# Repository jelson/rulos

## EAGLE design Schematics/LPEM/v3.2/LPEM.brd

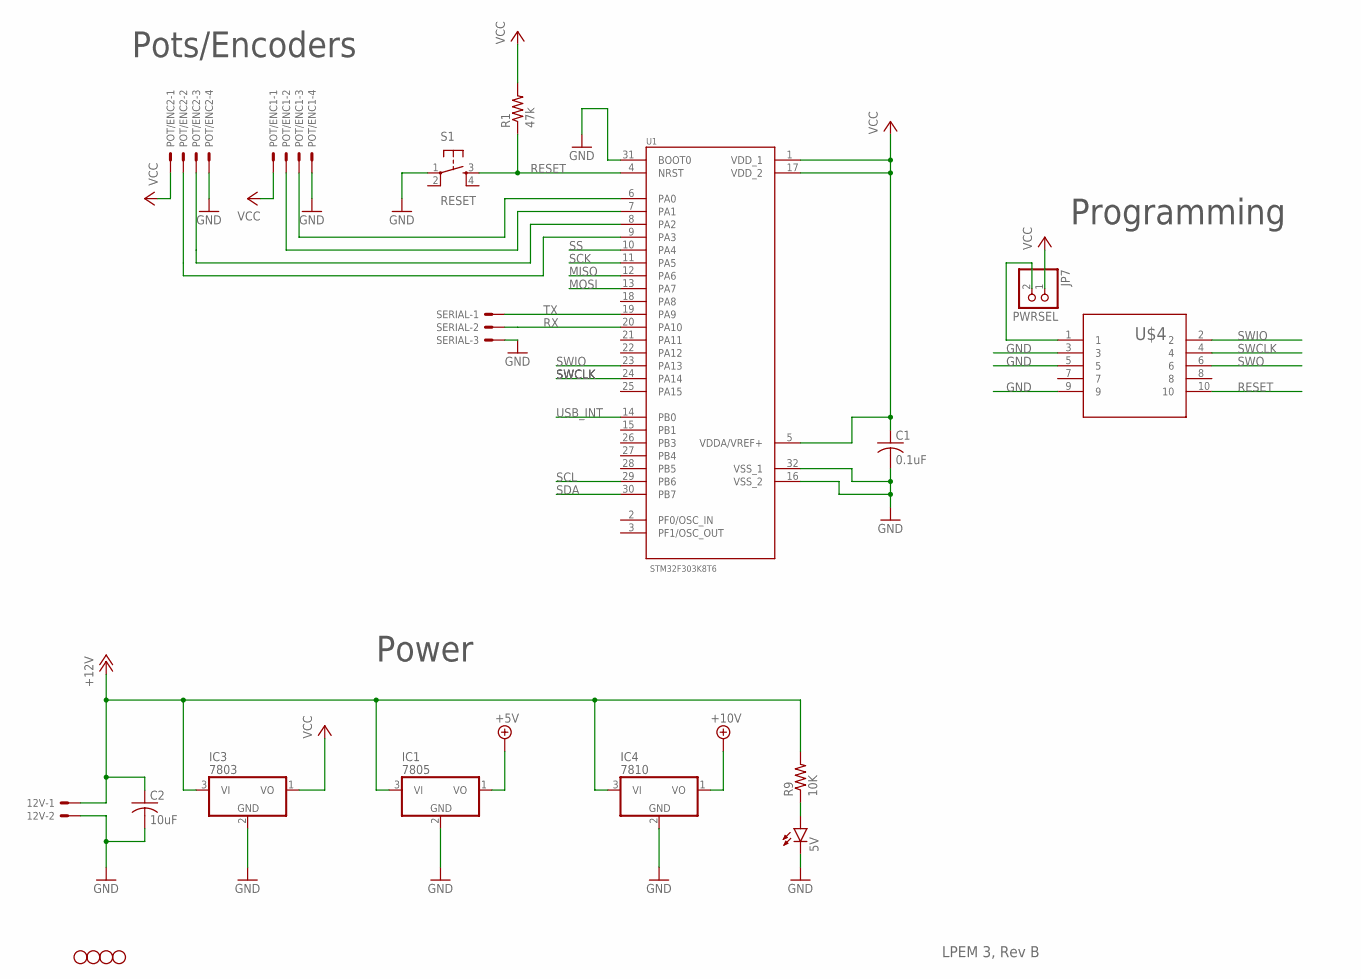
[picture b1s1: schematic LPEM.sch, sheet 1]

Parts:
5V: LED3MM
12V: 22-23-2021
C1: 0.1uF; C025-025X050
C2: 10uF; C025-025X050
IC1: 7805; TO92
IC3: 7803; TO92
IC4: 7810; TO92
JP1, JP2, JP8, JP9: STAND-OFF
JP7: PWRSEL; 1X02
POT/ENC1, POT/ENC2: 22-23-2041
R1: 47k; 0204/5
R9: 10K; 0204/5
S1: RESET; TACTILE-PTH
SERIAL: 22-23-2031
U1: STM32F303K8T6; QFP80P900X900X160-32N
U$4: CORTEX_HEADERJ; CORTEX_HEADER

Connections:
+5V: IC1.1 (VO); also elsewhere on the board
+10V: IC4.1 (VO); also elsewhere on the board
+12V: 12V.1, C2.1, IC1.3 (VI), IC3.3 (VI), IC4.3 (VI), R9.2; also elsewhere on the board
GND: 5V.K (C), 12V.2, C1.2, C2.2, IC1.2 (GND), IC3.2 (GND), IC4.2 (GND), POT/ENC1.4, POT/ENC2.4, S1.1, SERIAL.3, U1.16 (VSS_2), U1.31 (BOOT0), U1.32 (VSS_1), U$4.3, U$4.5, U$4.9; also elsewhere on the board
MISO: U1.12 (PA6); also elsewhere on the board
MOSI: U1.13 (PA7); also elsewhere on the board
unnamed: POT/ENC2.3, U1.8 (PA2)
unnamed: POT/ENC2.2, U1.9 (PA3)
unnamed: POT/ENC1.3, U1.6 (PA0)
unnamed: JP7.2, U$4.1
unnamed: 5V.A, R9.1
unnamed: POT/ENC1.2, U1.7 (PA1)
RESET: R1.1, S1.3, U1.4 (NRST), U$4.10
RX: SERIAL.2, U1.20 (PA10)
SCK: U1.11 (PA5); also elsewhere on the board
SCL: U1.29 (PB6); also elsewhere on the board
SDA: U1.30 (PB7); also elsewhere on the board
SS: U1.10 (PA4); also elsewhere on the board
SWCLK: U1.24 (PA14), U$4.4
SWIO: U1.23 (PA13), U$4.2
SWO: U$4.6
TX: SERIAL.1, U1.19 (PA9)
USB_INT: U1.14 (PB0); also elsewhere on the board
VCC: C1.1, IC3.1 (VO), JP7.1, POT/ENC1.1, POT/ENC2.1, R1.2, U1.1 (VDD_1), U1.5 (VDDA/VREF+), U1.17 (VDD_2); also elsewhere on the board

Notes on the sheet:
Power
Pots/Encoders
LPEM 3, Rev B
Programming

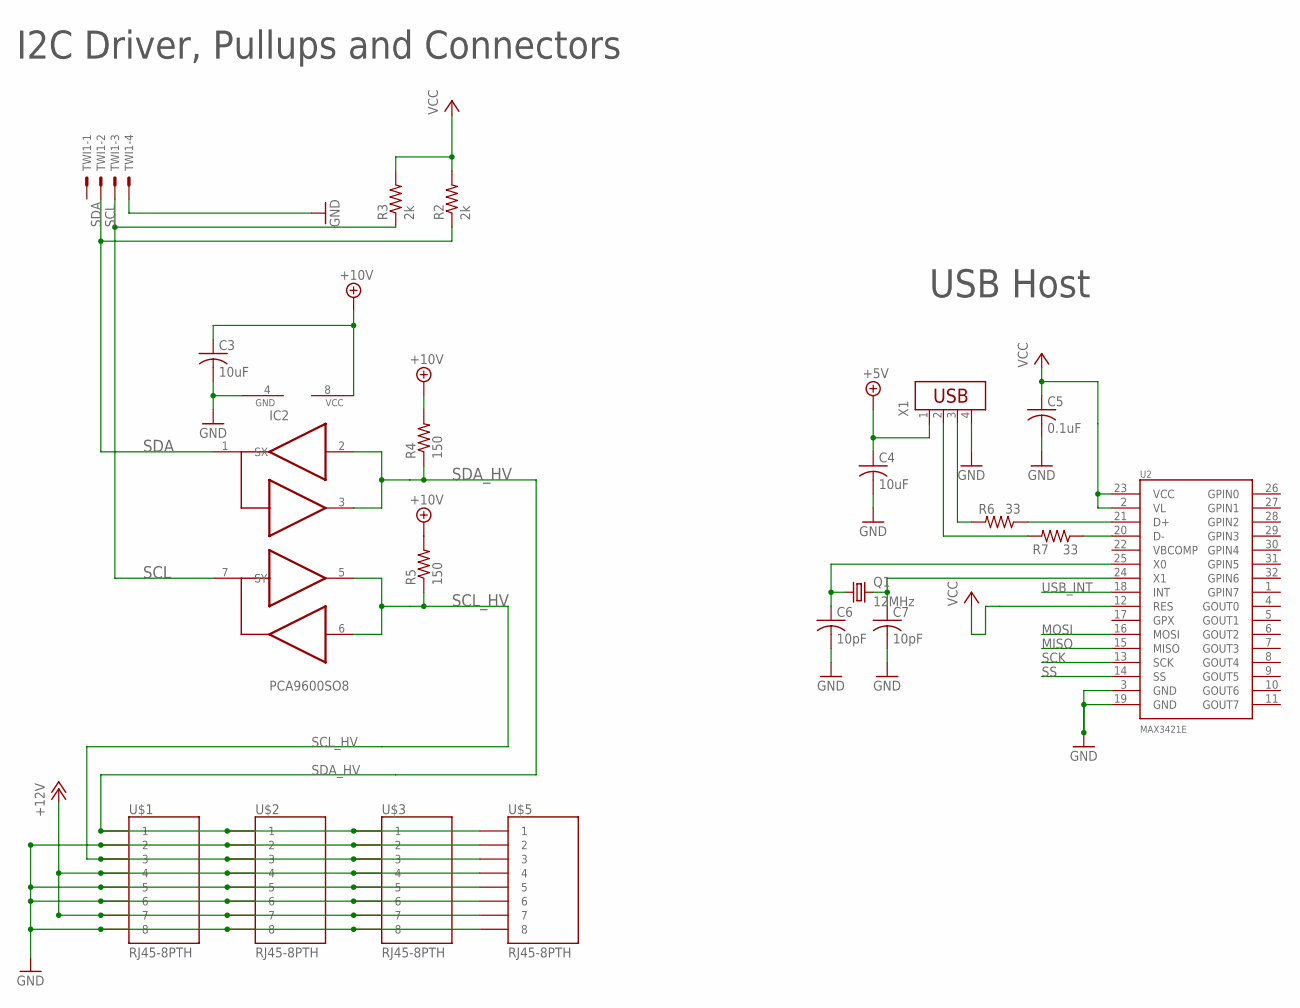
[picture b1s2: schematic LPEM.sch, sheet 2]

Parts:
C3, C4: 10uF; C025-025X050
C5: 0.1uF; C025-025X050
C6, C7: 10pF; C025-025X050
IC2: PCA9600SO8; SO08
Q1: 12MHz; HC18U-V
R2, R3: 2k; 0204/5
R4, R5: 150; 0204/5
R6, R7: 33; 0204/5
TWI1: 22-23-2041
U2: MAX3421E; TQFP32-5MM
U$1, U$2, U$3, U$5: RJ45-8PTH; RJ45-8
X1: USB-787616; USB

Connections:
+5V: C4.1, X1.1; also elsewhere on the board
+10V: C3.1, IC2.8 (VCC), R4.2, R5.2; also elsewhere on the board
+12V: U$1.4, U$1.7, U$2.4, U$2.7, U$3.4, U$3.7, U$5.4, U$5.7; also elsewhere on the board
GND: C3.2, C4.2, C5.2, C6.2, C7.2, IC2.4 (GND), TWI1.4, U2.3 (GND), U2.19 (GND), U$1.2, U$1.5, U$1.6, U$1.8, U$2.2, U$2.5, U$2.6, U$2.8, U$3.2, U$3.5, U$3.6, U$3.8, U$5.2, U$5.5, U$5.6, U$5.8, X1.4; also elsewhere on the board
MISO: U2.15 (MISO); also elsewhere on the board
MOSI: U2.16 (MOSI); also elsewhere on the board
unnamed: R6.2, X1.3
unnamed: R7.2, X1.2
unnamed: C6.1, Q1.1, U2.25 (X0)
unnamed: C7.1, Q1.2, U2.24 (X1)
unnamed: R6.1, U2.21 (D+)
unnamed: R7.1, U2.20 (D-)
SCK: U2.13 (SCK); also elsewhere on the board
SCL: IC2.7 (SY), R3.1, TWI1.3; also elsewhere on the board
SCL_HV: IC2.5 (TY), IC2.6 (RY), R5.1, U$1.3, U$2.3, U$3.3, U$5.3
SDA: IC2.1 (SX), R2.1, TWI1.2; also elsewhere on the board
SDA_HV: IC2.2 (RX), IC2.3 (TX), R4.1, U$1.1, U$2.1, U$3.1, U$5.1
SS: U2.14 (SS); also elsewhere on the board
USB_INT: U2.18 (INT); also elsewhere on the board
VCC: C5.1, R2.2, R3.2, U2.2 (VL), U2.12 (RES), U2.23 (VCC); also elsewhere on the board

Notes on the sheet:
I2C Driver, Pullups and Connectors
USB Host

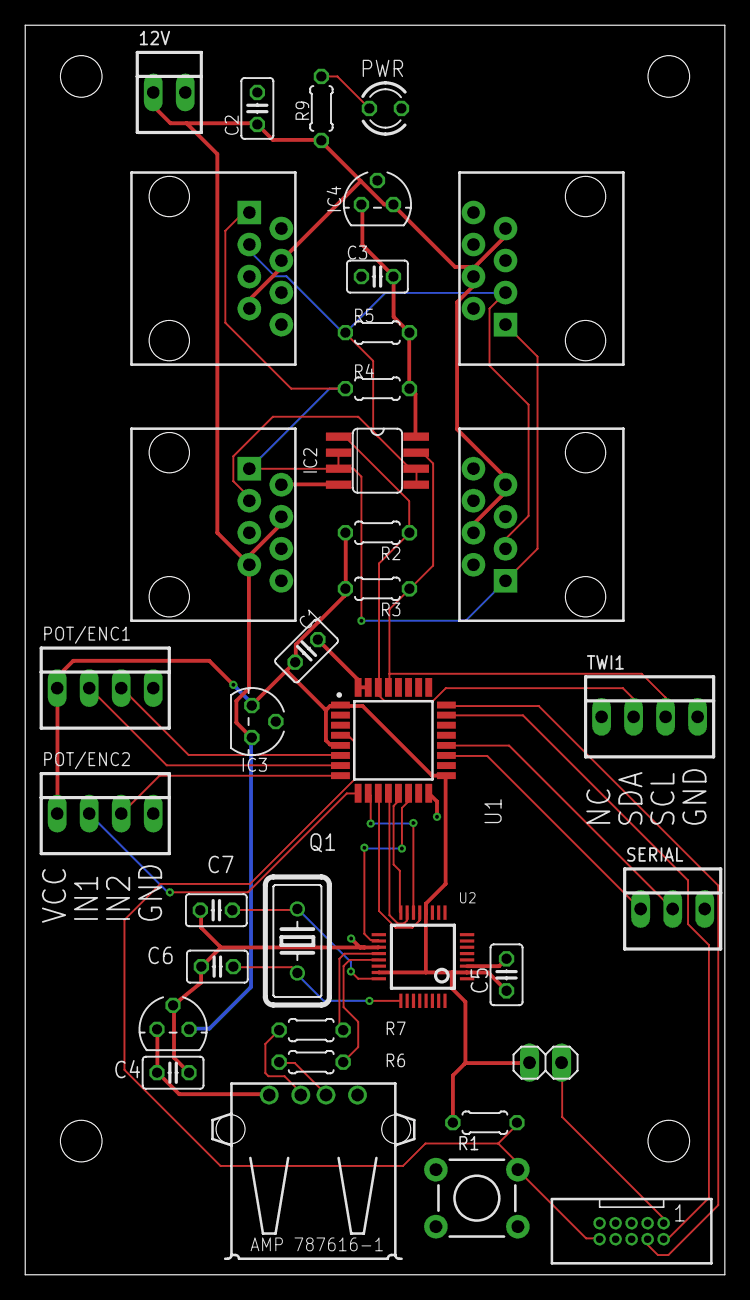
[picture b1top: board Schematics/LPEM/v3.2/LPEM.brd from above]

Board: 2 copper layers, 55.5 x 99.1 mm, 40 parts (0 on the bottom side), 31 nets.

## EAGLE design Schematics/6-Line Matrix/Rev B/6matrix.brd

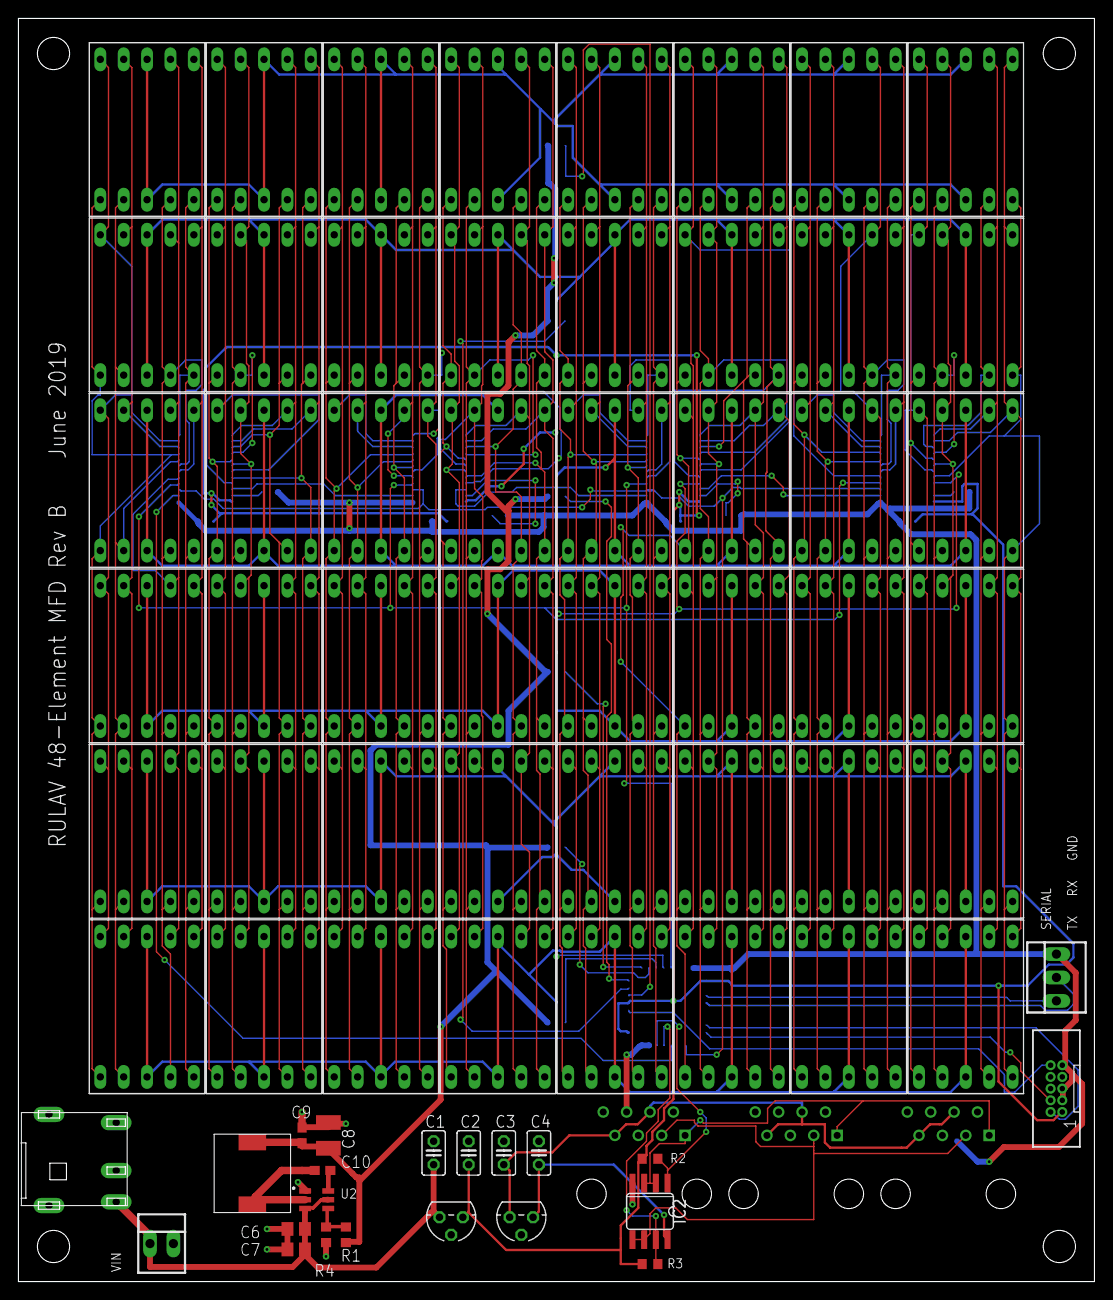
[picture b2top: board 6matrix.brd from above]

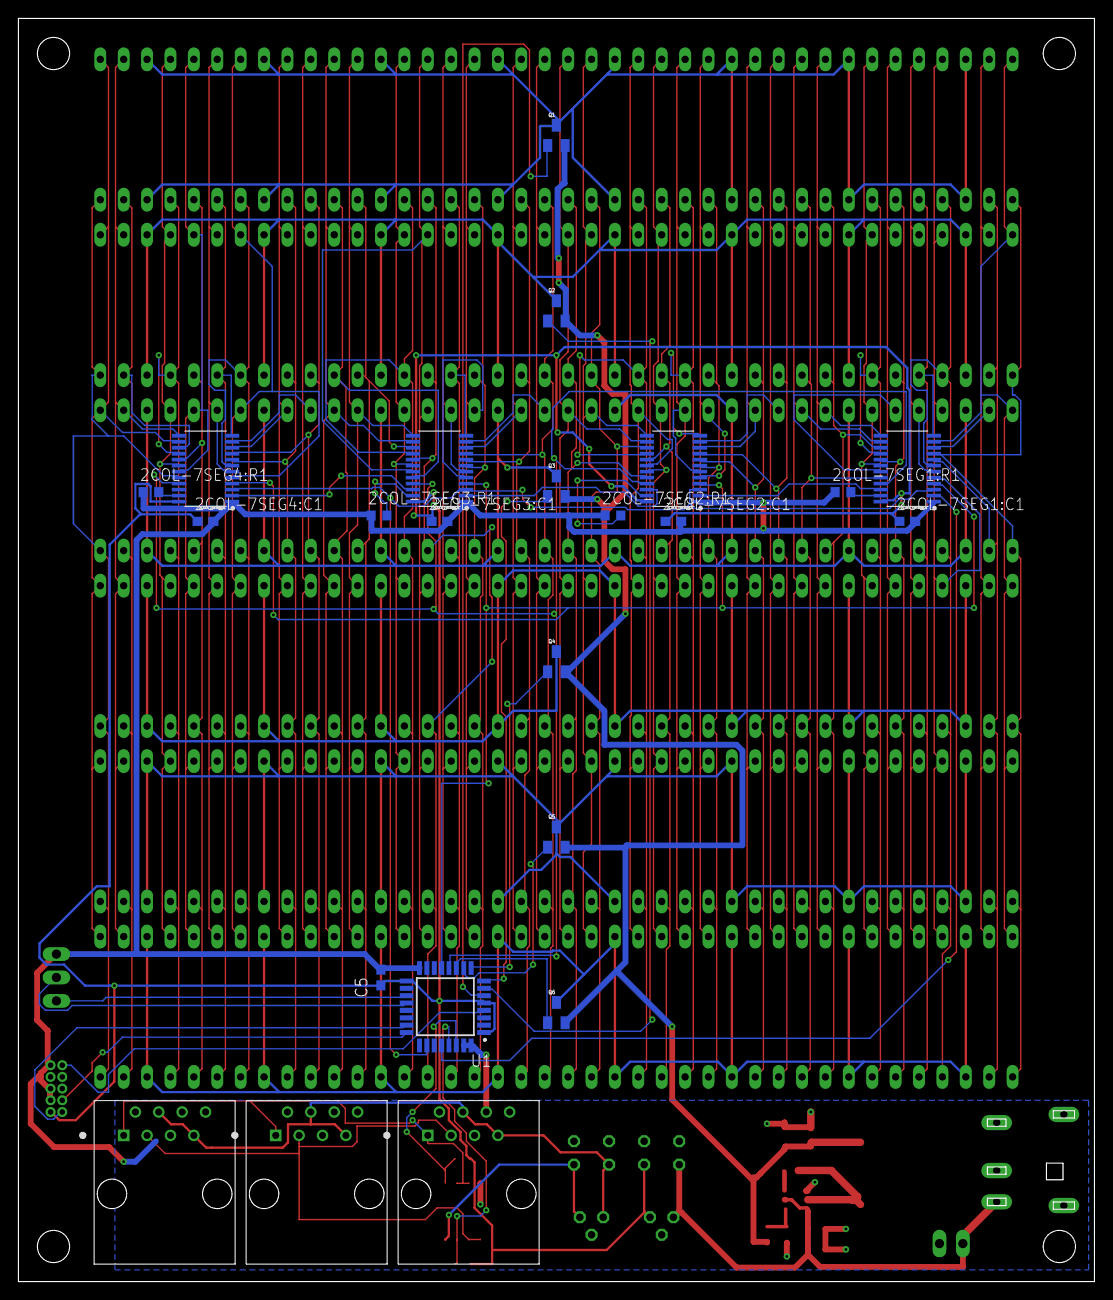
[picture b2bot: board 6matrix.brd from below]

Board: 2 copper layers, 116.8 x 137.1 mm, 93 parts (23 on the bottom side), 105 nets.

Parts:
2COL-7SEG1:C1, 2COL-7SEG2:C1, 2COL-7SEG3:C1, 2COL-7SEG4:C1: 1uF; C0603
2COL-7SEG1:IC1, 2COL-7SEG2:IC1, 2COL-7SEG3:IC1, 2COL-7SEG4:IC1: STP16CPC26XTR; SOP65P640X120-24
2COL-7SEG1:LED1, 2COL-7SEG1:LED2, 2COL-7SEG1:LED3, 2COL-7SEG1:LED4, 2COL-7SEG1:LED5, 2COL-7SEG1:LED6, 2COL-7SEG1:LED7, 2COL-7SEG1:LED8, 2COL-7SEG1:LED9, 2COL-7SEG1:LED10, 2COL-7SEG1:LED11, 2COL-7SEG1:LED12, 2COL-7SEG2:LED1, 2COL-7SEG2:LED2, 2COL-7SEG2:LED3, 2COL-7SEG2:LED4, 2COL-7SEG2:LED5, 2COL-7SEG2:LED6, 2COL-7SEG2:LED7, 2COL-7SEG2:LED8, 2COL-7SEG2:LED9, 2COL-7SEG2:LED10, 2COL-7SEG2:LED11, 2COL-7SEG2:LED12, 2COL-7SEG3:LED1, 2COL-7SEG3:LED2, 2COL-7SEG3:LED3, 2COL-7SEG3:LED4, 2COL-7SEG3:LED5, 2COL-7SEG3:LED6, 2COL-7SEG3:LED7, 2COL-7SEG3:LED8, 2COL-7SEG3:LED9, 2COL-7SEG3:LED10, 2COL-7SEG3:LED11, 2COL-7SEG3:LED12, 2COL-7SEG4:LED1, 2COL-7SEG4:LED2, 2COL-7SEG4:LED3, 2COL-7SEG4:LED4, 2COL-7SEG4:LED5, 2COL-7SEG4:LED6, 2COL-7SEG4:LED7, 2COL-7SEG4:LED8, 2COL-7SEG4:LED9, 2COL-7SEG4:LED10, 2COL-7SEG4:LED11, 2COL-7SEG4:LED12: 7-SEG_SA56-11; SA56-11
2COL-7SEG1:R1, 2COL-7SEG2:R1, 2COL-7SEG3:R1, 2COL-7SEG4:R1: R0603
C1, C4: 10uF; C025-025X050
C2, C3: 1uF; C025-025X050
C5: 1uF; C0603
C6, C7: 10uF; C0805
C8: 47uF; C1210
C9: C0603
C10: 0.1uF; C0603
IC2: PCA9600SO8; SO08
IC3: 7803; TO92
IC4: 7810; TO92
PROG: CORTEX_HEADERJ; CORTEX_HEADER
Q1, Q2, Q3, Q4, Q5, Q6: MOSFET-PCHANNEL; SOT23
R1: 22.6k; R0603
R2, R3: 2k; R0603
R4: 10k; R0603
SERIAL: 22-23-2031
U1: STM32F303K8T6; QFP80P900X900X160-32N
U2: TPS563200; SOT95P280X110-6N
U$1, U$2, U$3: 54602-908LF; AMPHENOL_54602-908LF
U$4: 2.2uH; DEM804XC
U$5: CUI-PJ-051
VIN: 22-23-2021

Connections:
2COL-7SEG1:N$1: 2COL-7SEG1:IC1.11, 2COL-7SEG1:LED1.10, 2COL-7SEG1:LED2.10, 2COL-7SEG1:LED3.10, 2COL-7SEG1:LED4.10, 2COL-7SEG1:LED5.10, 2COL-7SEG1:LED6.10
2COL-7SEG1:N$2: 2COL-7SEG1:IC1.12, 2COL-7SEG1:LED1.5, 2COL-7SEG1:LED2.5, 2COL-7SEG1:LED3.5, 2COL-7SEG1:LED4.5, 2COL-7SEG1:LED5.5, 2COL-7SEG1:LED6.5
2COL-7SEG1:N$3: 2COL-7SEG1:IC1.19, 2COL-7SEG1:LED7.10, 2COL-7SEG1:LED8.10, 2COL-7SEG1:LED9.10, 2COL-7SEG1:LED10.10, 2COL-7SEG1:LED11.10, 2COL-7SEG1:LED12.10
2COL-7SEG1:N$4: 2COL-7SEG1:IC1.18, 2COL-7SEG1:LED7.9, 2COL-7SEG1:LED8.9, 2COL-7SEG1:LED9.9, 2COL-7SEG1:LED10.9, 2COL-7SEG1:LED11.9, 2COL-7SEG1:LED12.9
2COL-7SEG1:N$5: 2COL-7SEG1:IC1.17, 2COL-7SEG1:LED7.1, 2COL-7SEG1:LED8.1, 2COL-7SEG1:LED9.1, 2COL-7SEG1:LED10.1, 2COL-7SEG1:LED11.1, 2COL-7SEG1:LED12.1
2COL-7SEG1:N$6: 2COL-7SEG1:IC1.5, 2COL-7SEG1:LED1.7, 2COL-7SEG1:LED2.7, 2COL-7SEG1:LED3.7, 2COL-7SEG1:LED4.7, 2COL-7SEG1:LED5.7, 2COL-7SEG1:LED6.7
2COL-7SEG1:N$7: 2COL-7SEG1:IC1.6, 2COL-7SEG1:LED1.6, 2COL-7SEG1:LED2.6, 2COL-7SEG1:LED3.6, 2COL-7SEG1:LED4.6, 2COL-7SEG1:LED5.6, 2COL-7SEG1:LED6.6
2COL-7SEG1:N$8: 2COL-7SEG1:IC1.10, 2COL-7SEG1:LED1.9, 2COL-7SEG1:LED2.9, 2COL-7SEG1:LED3.9, 2COL-7SEG1:LED4.9, 2COL-7SEG1:LED5.9, 2COL-7SEG1:LED6.9
2COL-7SEG1:N$9: 2COL-7SEG1:IC1.9, 2COL-7SEG1:LED1.1, 2COL-7SEG1:LED2.1, 2COL-7SEG1:LED3.1, 2COL-7SEG1:LED4.1, 2COL-7SEG1:LED5.1, 2COL-7SEG1:LED6.1
2COL-7SEG1:N$10: 2COL-7SEG1:IC1.8, 2COL-7SEG1:LED1.2, 2COL-7SEG1:LED2.2, 2COL-7SEG1:LED3.2, 2COL-7SEG1:LED4.2, 2COL-7SEG1:LED5.2, 2COL-7SEG1:LED6.2
2COL-7SEG1:N$11: 2COL-7SEG1:IC1.7, 2COL-7SEG1:LED1.4, 2COL-7SEG1:LED2.4, 2COL-7SEG1:LED3.4, 2COL-7SEG1:LED4.4, 2COL-7SEG1:LED5.4, 2COL-7SEG1:LED6.4
2COL-7SEG1:N$12: 2COL-7SEG1:IC1.16, 2COL-7SEG1:LED7.2, 2COL-7SEG1:LED8.2, 2COL-7SEG1:LED9.2, 2COL-7SEG1:LED10.2, 2COL-7SEG1:LED11.2, 2COL-7SEG1:LED12.2
2COL-7SEG1:N$13: 2COL-7SEG1:IC1.15, 2COL-7SEG1:LED7.4, 2COL-7SEG1:LED8.4, 2COL-7SEG1:LED9.4, 2COL-7SEG1:LED10.4, 2COL-7SEG1:LED11.4, 2COL-7SEG1:LED12.4
2COL-7SEG1:N$14: 2COL-7SEG1:IC1.14, 2COL-7SEG1:LED7.6, 2COL-7SEG1:LED8.6, 2COL-7SEG1:LED9.6, 2COL-7SEG1:LED10.6, 2COL-7SEG1:LED11.6, 2COL-7SEG1:LED12.6
2COL-7SEG1:N$15: 2COL-7SEG1:IC1.13, 2COL-7SEG1:LED7.7, 2COL-7SEG1:LED8.7, 2COL-7SEG1:LED9.7, 2COL-7SEG1:LED10.7, 2COL-7SEG1:LED11.7, 2COL-7SEG1:LED12.7
2COL-7SEG1:N$16: 2COL-7SEG1:IC1.20, 2COL-7SEG1:LED7.5, 2COL-7SEG1:LED8.5, 2COL-7SEG1:LED9.5, 2COL-7SEG1:LED10.5, 2COL-7SEG1:LED11.5, 2COL-7SEG1:LED12.5
2COL-7SEG1:R-EXT: 2COL-7SEG1:IC1.23, 2COL-7SEG1:R1.2
2COL-7SEG2:N$1: 2COL-7SEG2:IC1.11, 2COL-7SEG2:LED1.10, 2COL-7SEG2:LED2.10, 2COL-7SEG2:LED3.10, 2COL-7SEG2:LED4.10, 2COL-7SEG2:LED5.10, 2COL-7SEG2:LED6.10
2COL-7SEG2:N$2: 2COL-7SEG2:IC1.12, 2COL-7SEG2:LED1.5, 2COL-7SEG2:LED2.5, 2COL-7SEG2:LED3.5, 2COL-7SEG2:LED4.5, 2COL-7SEG2:LED5.5, 2COL-7SEG2:LED6.5
2COL-7SEG2:N$3: 2COL-7SEG2:IC1.19, 2COL-7SEG2:LED7.10, 2COL-7SEG2:LED8.10, 2COL-7SEG2:LED9.10, 2COL-7SEG2:LED10.10, 2COL-7SEG2:LED11.10, 2COL-7SEG2:LED12.10
2COL-7SEG2:N$4: 2COL-7SEG2:IC1.18, 2COL-7SEG2:LED7.9, 2COL-7SEG2:LED8.9, 2COL-7SEG2:LED9.9, 2COL-7SEG2:LED10.9, 2COL-7SEG2:LED11.9, 2COL-7SEG2:LED12.9
2COL-7SEG2:N$5: 2COL-7SEG2:IC1.17, 2COL-7SEG2:LED7.1, 2COL-7SEG2:LED8.1, 2COL-7SEG2:LED9.1, 2COL-7SEG2:LED10.1, 2COL-7SEG2:LED11.1, 2COL-7SEG2:LED12.1
2COL-7SEG2:N$6: 2COL-7SEG2:IC1.5, 2COL-7SEG2:LED1.7, 2COL-7SEG2:LED2.7, 2COL-7SEG2:LED3.7, 2COL-7SEG2:LED4.7, 2COL-7SEG2:LED5.7, 2COL-7SEG2:LED6.7
2COL-7SEG2:N$7: 2COL-7SEG2:IC1.6, 2COL-7SEG2:LED1.6, 2COL-7SEG2:LED2.6, 2COL-7SEG2:LED3.6, 2COL-7SEG2:LED4.6, 2COL-7SEG2:LED5.6, 2COL-7SEG2:LED6.6
2COL-7SEG2:N$8: 2COL-7SEG2:IC1.10, 2COL-7SEG2:LED1.9, 2COL-7SEG2:LED2.9, 2COL-7SEG2:LED3.9, 2COL-7SEG2:LED4.9, 2COL-7SEG2:LED5.9, 2COL-7SEG2:LED6.9
2COL-7SEG2:N$9: 2COL-7SEG2:IC1.9, 2COL-7SEG2:LED1.1, 2COL-7SEG2:LED2.1, 2COL-7SEG2:LED3.1, 2COL-7SEG2:LED4.1, 2COL-7SEG2:LED5.1, 2COL-7SEG2:LED6.1
2COL-7SEG2:N$10: 2COL-7SEG2:IC1.8, 2COL-7SEG2:LED1.2, 2COL-7SEG2:LED2.2, 2COL-7SEG2:LED3.2, 2COL-7SEG2:LED4.2, 2COL-7SEG2:LED5.2, 2COL-7SEG2:LED6.2
2COL-7SEG2:N$11: 2COL-7SEG2:IC1.7, 2COL-7SEG2:LED1.4, 2COL-7SEG2:LED2.4, 2COL-7SEG2:LED3.4, 2COL-7SEG2:LED4.4, 2COL-7SEG2:LED5.4, 2COL-7SEG2:LED6.4
2COL-7SEG2:N$12: 2COL-7SEG2:IC1.16, 2COL-7SEG2:LED7.2, 2COL-7SEG2:LED8.2, 2COL-7SEG2:LED9.2, 2COL-7SEG2:LED10.2, 2COL-7SEG2:LED11.2, 2COL-7SEG2:LED12.2
2COL-7SEG2:N$13: 2COL-7SEG2:IC1.15, 2COL-7SEG2:LED7.4, 2COL-7SEG2:LED8.4, 2COL-7SEG2:LED9.4, 2COL-7SEG2:LED10.4, 2COL-7SEG2:LED11.4, 2COL-7SEG2:LED12.4
2COL-7SEG2:N$14: 2COL-7SEG2:IC1.14, 2COL-7SEG2:LED7.6, 2COL-7SEG2:LED8.6, 2COL-7SEG2:LED9.6, 2COL-7SEG2:LED10.6, 2COL-7SEG2:LED11.6, 2COL-7SEG2:LED12.6
2COL-7SEG2:N$15: 2COL-7SEG2:IC1.13, 2COL-7SEG2:LED7.7, 2COL-7SEG2:LED8.7, 2COL-7SEG2:LED9.7, 2COL-7SEG2:LED10.7, 2COL-7SEG2:LED11.7, 2COL-7SEG2:LED12.7
2COL-7SEG2:N$16: 2COL-7SEG2:IC1.20, 2COL-7SEG2:LED7.5, 2COL-7SEG2:LED8.5, 2COL-7SEG2:LED9.5, 2COL-7SEG2:LED10.5, 2COL-7SEG2:LED11.5, 2COL-7SEG2:LED12.5
2COL-7SEG2:R-EXT: 2COL-7SEG2:IC1.23, 2COL-7SEG2:R1.2
2COL-7SEG3:N$1: 2COL-7SEG3:IC1.11, 2COL-7SEG3:LED1.10, 2COL-7SEG3:LED2.10, 2COL-7SEG3:LED3.10, 2COL-7SEG3:LED4.10, 2COL-7SEG3:LED5.10, 2COL-7SEG3:LED6.10
2COL-7SEG3:N$2: 2COL-7SEG3:IC1.12, 2COL-7SEG3:LED1.5, 2COL-7SEG3:LED2.5, 2COL-7SEG3:LED3.5, 2COL-7SEG3:LED4.5, 2COL-7SEG3:LED5.5, 2COL-7SEG3:LED6.5
2COL-7SEG3:N$3: 2COL-7SEG3:IC1.19, 2COL-7SEG3:LED7.10, 2COL-7SEG3:LED8.10, 2COL-7SEG3:LED9.10, 2COL-7SEG3:LED10.10, 2COL-7SEG3:LED11.10, 2COL-7SEG3:LED12.10
2COL-7SEG3:N$4: 2COL-7SEG3:IC1.18, 2COL-7SEG3:LED7.9, 2COL-7SEG3:LED8.9, 2COL-7SEG3:LED9.9, 2COL-7SEG3:LED10.9, 2COL-7SEG3:LED11.9, 2COL-7SEG3:LED12.9
2COL-7SEG3:N$5: 2COL-7SEG3:IC1.17, 2COL-7SEG3:LED7.1, 2COL-7SEG3:LED8.1, 2COL-7SEG3:LED9.1, 2COL-7SEG3:LED10.1, 2COL-7SEG3:LED11.1, 2COL-7SEG3:LED12.1
2COL-7SEG3:N$6: 2COL-7SEG3:IC1.5, 2COL-7SEG3:LED1.7, 2COL-7SEG3:LED2.7, 2COL-7SEG3:LED3.7, 2COL-7SEG3:LED4.7, 2COL-7SEG3:LED5.7, 2COL-7SEG3:LED6.7
2COL-7SEG3:N$7: 2COL-7SEG3:IC1.6, 2COL-7SEG3:LED1.6, 2COL-7SEG3:LED2.6, 2COL-7SEG3:LED3.6, 2COL-7SEG3:LED4.6, 2COL-7SEG3:LED5.6, 2COL-7SEG3:LED6.6
2COL-7SEG3:N$8: 2COL-7SEG3:IC1.10, 2COL-7SEG3:LED1.9, 2COL-7SEG3:LED2.9, 2COL-7SEG3:LED3.9, 2COL-7SEG3:LED4.9, 2COL-7SEG3:LED5.9, 2COL-7SEG3:LED6.9
2COL-7SEG3:N$9: 2COL-7SEG3:IC1.9, 2COL-7SEG3:LED1.1, 2COL-7SEG3:LED2.1, 2COL-7SEG3:LED3.1, 2COL-7SEG3:LED4.1, 2COL-7SEG3:LED5.1, 2COL-7SEG3:LED6.1
2COL-7SEG3:N$10: 2COL-7SEG3:IC1.8, 2COL-7SEG3:LED1.2, 2COL-7SEG3:LED2.2, 2COL-7SEG3:LED3.2, 2COL-7SEG3:LED4.2, 2COL-7SEG3:LED5.2, 2COL-7SEG3:LED6.2
2COL-7SEG3:N$11: 2COL-7SEG3:IC1.7, 2COL-7SEG3:LED1.4, 2COL-7SEG3:LED2.4, 2COL-7SEG3:LED3.4, 2COL-7SEG3:LED4.4, 2COL-7SEG3:LED5.4, 2COL-7SEG3:LED6.4
2COL-7SEG3:N$12: 2COL-7SEG3:IC1.16, 2COL-7SEG3:LED7.2, 2COL-7SEG3:LED8.2, 2COL-7SEG3:LED9.2, 2COL-7SEG3:LED10.2, 2COL-7SEG3:LED11.2, 2COL-7SEG3:LED12.2
2COL-7SEG3:N$13: 2COL-7SEG3:IC1.15, 2COL-7SEG3:LED7.4, 2COL-7SEG3:LED8.4, 2COL-7SEG3:LED9.4, 2COL-7SEG3:LED10.4, 2COL-7SEG3:LED11.4, 2COL-7SEG3:LED12.4
2COL-7SEG3:N$14: 2COL-7SEG3:IC1.14, 2COL-7SEG3:LED7.6, 2COL-7SEG3:LED8.6, 2COL-7SEG3:LED9.6, 2COL-7SEG3:LED10.6, 2COL-7SEG3:LED11.6, 2COL-7SEG3:LED12.6
2COL-7SEG3:N$15: 2COL-7SEG3:IC1.13, 2COL-7SEG3:LED7.7, 2COL-7SEG3:LED8.7, 2COL-7SEG3:LED9.7, 2COL-7SEG3:LED10.7, 2COL-7SEG3:LED11.7, 2COL-7SEG3:LED12.7
2COL-7SEG3:N$16: 2COL-7SEG3:IC1.20, 2COL-7SEG3:LED7.5, 2COL-7SEG3:LED8.5, 2COL-7SEG3:LED9.5, 2COL-7SEG3:LED10.5, 2COL-7SEG3:LED11.5, 2COL-7SEG3:LED12.5
2COL-7SEG3:R-EXT: 2COL-7SEG3:IC1.23, 2COL-7SEG3:R1.2
2COL-7SEG4:N$1: 2COL-7SEG4:IC1.11, 2COL-7SEG4:LED1.10, 2COL-7SEG4:LED2.10, 2COL-7SEG4:LED3.10, 2COL-7SEG4:LED4.10, 2COL-7SEG4:LED5.10, 2COL-7SEG4:LED6.10
2COL-7SEG4:N$2: 2COL-7SEG4:IC1.12, 2COL-7SEG4:LED1.5, 2COL-7SEG4:LED2.5, 2COL-7SEG4:LED3.5, 2COL-7SEG4:LED4.5, 2COL-7SEG4:LED5.5, 2COL-7SEG4:LED6.5
2COL-7SEG4:N$3: 2COL-7SEG4:IC1.19, 2COL-7SEG4:LED7.10, 2COL-7SEG4:LED8.10, 2COL-7SEG4:LED9.10, 2COL-7SEG4:LED10.10, 2COL-7SEG4:LED11.10, 2COL-7SEG4:LED12.10
2COL-7SEG4:N$4: 2COL-7SEG4:IC1.18, 2COL-7SEG4:LED7.9, 2COL-7SEG4:LED8.9, 2COL-7SEG4:LED9.9, 2COL-7SEG4:LED10.9, 2COL-7SEG4:LED11.9, 2COL-7SEG4:LED12.9
2COL-7SEG4:N$5: 2COL-7SEG4:IC1.17, 2COL-7SEG4:LED7.1, 2COL-7SEG4:LED8.1, 2COL-7SEG4:LED9.1, 2COL-7SEG4:LED10.1, 2COL-7SEG4:LED11.1, 2COL-7SEG4:LED12.1
2COL-7SEG4:N$6: 2COL-7SEG4:IC1.5, 2COL-7SEG4:LED1.7, 2COL-7SEG4:LED2.7, 2COL-7SEG4:LED3.7, 2COL-7SEG4:LED4.7, 2COL-7SEG4:LED5.7, 2COL-7SEG4:LED6.7
2COL-7SEG4:N$7: 2COL-7SEG4:IC1.6, 2COL-7SEG4:LED1.6, 2COL-7SEG4:LED2.6, 2COL-7SEG4:LED3.6, 2COL-7SEG4:LED4.6, 2COL-7SEG4:LED5.6, 2COL-7SEG4:LED6.6
2COL-7SEG4:N$8: 2COL-7SEG4:IC1.10, 2COL-7SEG4:LED1.9, 2COL-7SEG4:LED2.9, 2COL-7SEG4:LED3.9, 2COL-7SEG4:LED4.9, 2COL-7SEG4:LED5.9, 2COL-7SEG4:LED6.9
2COL-7SEG4:N$9: 2COL-7SEG4:IC1.9, 2COL-7SEG4:LED1.1, 2COL-7SEG4:LED2.1, 2COL-7SEG4:LED3.1, 2COL-7SEG4:LED4.1, 2COL-7SEG4:LED5.1, 2COL-7SEG4:LED6.1
2COL-7SEG4:N$10: 2COL-7SEG4:IC1.8, 2COL-7SEG4:LED1.2, 2COL-7SEG4:LED2.2, 2COL-7SEG4:LED3.2, 2COL-7SEG4:LED4.2, 2COL-7SEG4:LED5.2, 2COL-7SEG4:LED6.2
2COL-7SEG4:N$11: 2COL-7SEG4:IC1.7, 2COL-7SEG4:LED1.4, 2COL-7SEG4:LED2.4, 2COL-7SEG4:LED3.4, 2COL-7SEG4:LED4.4, 2COL-7SEG4:LED5.4, 2COL-7SEG4:LED6.4
2COL-7SEG4:N$12: 2COL-7SEG4:IC1.16, 2COL-7SEG4:LED7.2, 2COL-7SEG4:LED8.2, 2COL-7SEG4:LED9.2, 2COL-7SEG4:LED10.2, 2COL-7SEG4:LED11.2, 2COL-7SEG4:LED12.2
2COL-7SEG4:N$13: 2COL-7SEG4:IC1.15, 2COL-7SEG4:LED7.4, 2COL-7SEG4:LED8.4, 2COL-7SEG4:LED9.4, 2COL-7SEG4:LED10.4, 2COL-7SEG4:LED11.4, 2COL-7SEG4:LED12.4
2COL-7SEG4:N$14: 2COL-7SEG4:IC1.14, 2COL-7SEG4:LED7.6, 2COL-7SEG4:LED8.6, 2COL-7SEG4:LED9.6, 2COL-7SEG4:LED10.6, 2COL-7SEG4:LED11.6, 2COL-7SEG4:LED12.6
2COL-7SEG4:N$15: 2COL-7SEG4:IC1.13, 2COL-7SEG4:LED7.7, 2COL-7SEG4:LED8.7, 2COL-7SEG4:LED9.7, 2COL-7SEG4:LED10.7, 2COL-7SEG4:LED11.7, 2COL-7SEG4:LED12.7
2COL-7SEG4:N$16: 2COL-7SEG4:IC1.20, 2COL-7SEG4:LED7.5, 2COL-7SEG4:LED8.5, 2COL-7SEG4:LED9.5, 2COL-7SEG4:LED10.5, 2COL-7SEG4:LED11.5, 2COL-7SEG4:LED12.5
2COL-7SEG4:R-EXT: 2COL-7SEG4:IC1.23, 2COL-7SEG4:R1.2
+5V: C1.1, C6.1, C7.1, IC3.3, U2.3, U2.5, U$5.P$1, VIN.1
+10V: C4.1, IC2.8, IC4.1
+12V: C3.1, IC4.3, U$1.4, U$1.7, U$2.4, U$2.7, U$3.4, U$3.7
CLK: 2COL-7SEG1:IC1.3, 2COL-7SEG2:IC1.3, 2COL-7SEG3:IC1.3, 2COL-7SEG4:IC1.3, U1.26
GND: 2COL-7SEG1:C1.2, 2COL-7SEG1:IC1.1, 2COL-7SEG1:R1.1, 2COL-7SEG2:C1.2, 2COL-7SEG2:IC1.1, 2COL-7SEG2:R1.1, 2COL-7SEG3:C1.2, 2COL-7SEG3:IC1.1, 2COL-7SEG3:R1.1, 2COL-7SEG4:C1.2, 2COL-7SEG4:IC1.1, 2COL-7SEG4:R1.1, C1.2, C2.2, C3.2, C4.2, C5.2, C6.2, C7.2, C8.2, C9.2, IC2.4, IC3.2, IC4.2, PROG.3, PROG.5, PROG.9, R4.1, SERIAL.3, U1.16, U1.31, U1.32, U2.1, U$1.2, U$1.5, U$1.6, U$1.8, U$2.2, U$2.5, U$2.6, U$2.8, U$3.2, U$3.5, U$3.6, U$3.8, U$5.P$2, VIN.2
LE: 2COL-7SEG1:IC1.4, 2COL-7SEG2:IC1.4, 2COL-7SEG3:IC1.4, 2COL-7SEG4:IC1.4, U1.13
LEDPWR: C8.1, C9.1, Q1.2, Q2.2, Q3.2, Q4.2, Q5.2, Q6.2, R1.2, U$4.P$2
unnamed: 2COL-7SEG1:LED6.3, 2COL-7SEG1:LED6.8, 2COL-7SEG1:LED12.3, 2COL-7SEG1:LED12.8, 2COL-7SEG2:LED6.3, 2COL-7SEG2:LED6.8, 2COL-7SEG2:LED12.3, 2COL-7SEG2:LED12.8, 2COL-7SEG3:LED6.3, 2COL-7SEG3:LED6.8, 2COL-7SEG3:LED12.3, 2COL-7SEG3:LED12.8, 2COL-7SEG4:LED6.3, 2COL-7SEG4:LED6.8, 2COL-7SEG4:LED12.3, 2COL-7SEG4:LED12.8, Q6.3
unnamed: 2COL-7SEG1:LED5.3, 2COL-7SEG1:LED5.8, 2COL-7SEG1:LED11.3, 2COL-7SEG1:LED11.8, 2COL-7SEG2:LED5.3, 2COL-7SEG2:LED5.8, 2COL-7SEG2:LED11.3, 2COL-7SEG2:LED11.8, 2COL-7SEG3:LED5.3, 2COL-7SEG3:LED5.8, 2COL-7SEG3:LED11.3, 2COL-7SEG3:LED11.8, 2COL-7SEG4:LED5.3, 2COL-7SEG4:LED5.8, 2COL-7SEG4:LED11.3, 2COL-7SEG4:LED11.8, Q5.3
unnamed: 2COL-7SEG1:LED4.3, 2COL-7SEG1:LED4.8, 2COL-7SEG1:LED10.3, 2COL-7SEG1:LED10.8, 2COL-7SEG2:LED4.3, 2COL-7SEG2:LED4.8, 2COL-7SEG2:LED10.3, 2COL-7SEG2:LED10.8, 2COL-7SEG3:LED4.3, 2COL-7SEG3:LED4.8, 2COL-7SEG3:LED10.3, 2COL-7SEG3:LED10.8, 2COL-7SEG4:LED4.3, 2COL-7SEG4:LED4.8, 2COL-7SEG4:LED10.3, 2COL-7SEG4:LED10.8, Q4.3
unnamed: 2COL-7SEG1:LED3.3, 2COL-7SEG1:LED3.8, 2COL-7SEG1:LED9.3, 2COL-7SEG1:LED9.8, 2COL-7SEG2:LED3.3, 2COL-7SEG2:LED3.8, 2COL-7SEG2:LED9.3, 2COL-7SEG2:LED9.8, 2COL-7SEG3:LED3.3, 2COL-7SEG3:LED3.8, 2COL-7SEG3:LED9.3, 2COL-7SEG3:LED9.8, 2COL-7SEG4:LED3.3, 2COL-7SEG4:LED3.8, 2COL-7SEG4:LED9.3, 2COL-7SEG4:LED9.8, Q3.3
unnamed: 2COL-7SEG1:LED2.3, 2COL-7SEG1:LED2.8, 2COL-7SEG1:LED8.3, 2COL-7SEG1:LED8.8, 2COL-7SEG2:LED2.3, 2COL-7SEG2:LED2.8, 2COL-7SEG2:LED8.3, 2COL-7SEG2:LED8.8, 2COL-7SEG3:LED2.3, 2COL-7SEG3:LED2.8, 2COL-7SEG3:LED8.3, 2COL-7SEG3:LED8.8, 2COL-7SEG4:LED2.3, 2COL-7SEG4:LED2.8, 2COL-7SEG4:LED8.3, 2COL-7SEG4:LED8.8, Q2.3
unnamed: 2COL-7SEG1:LED1.3, 2COL-7SEG1:LED1.8, 2COL-7SEG1:LED7.3, 2COL-7SEG1:LED7.8, 2COL-7SEG2:LED1.3, 2COL-7SEG2:LED1.8, 2COL-7SEG2:LED7.3, 2COL-7SEG2:LED7.8, 2COL-7SEG3:LED1.3, 2COL-7SEG3:LED1.8, 2COL-7SEG3:LED7.3, 2COL-7SEG3:LED7.8, 2COL-7SEG4:LED1.3, 2COL-7SEG4:LED1.8, 2COL-7SEG4:LED7.3, 2COL-7SEG4:LED7.8, Q1.3
unnamed: C10.2, U2.6
unnamed: 2COL-7SEG1:IC1.22, 2COL-7SEG2:IC1.2
unnamed: 2COL-7SEG2:IC1.22, 2COL-7SEG3:IC1.2
unnamed: 2COL-7SEG3:IC1.22, 2COL-7SEG4:IC1.2
unnamed: R1.1, R4.2, U2.4
unnamed: C10.1, U2.2, U$4.P$1
OE: 2COL-7SEG1:IC1.21, 2COL-7SEG2:IC1.21, 2COL-7SEG3:IC1.21, 2COL-7SEG4:IC1.21, U1.12
RESET: PROG.10, U1.4
ROW1_EN: Q1.1, U1.6
ROW2_EN: Q2.1, U1.7
ROW3_EN: Q3.1, U1.8
ROW4_EN: Q4.1, U1.9
ROW5_EN: Q5.1, U1.10
ROW6_EN: Q6.1, U1.11
RX: SERIAL.2, U1.20
SCL: IC2.7, R3.1, U1.29
SCL_HV: IC2.5, IC2.6, U$1.3, U$2.3, U$3.3
SDA: IC2.1, R2.1, U1.30
SDA_HV: IC2.2, IC2.3, U$1.1, U$2.1, U$3.1
SDI: 2COL-7SEG1:IC1.2, U1.28
SWCLK: PROG.4, U1.24
SWIO: PROG.2, U1.23
TX: SERIAL.1, U1.19
VCC: 2COL-7SEG1:C1.1, 2COL-7SEG1:IC1.24, 2COL-7SEG2:C1.1, 2COL-7SEG2:IC1.24, 2COL-7SEG3:C1.1, 2COL-7SEG3:IC1.24, 2COL-7SEG4:C1.1, 2COL-7SEG4:IC1.24, C2.1, C5.1, IC3.1, PROG.1, R2.2, R3.2, U1.1, U1.5, U1.17

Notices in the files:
parts and their libraries:
SparkFun: Licensing: CC v3.0 Share-Alike You are welcome to use this library for commercial purposes.
